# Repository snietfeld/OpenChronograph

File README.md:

# What's this?
OpenChronograph is an a Arduino-compatible hybrid smartwatch platform built around Soprod micromotors. The majority of hybrid smartwatches available today (Skagen, Fossil) use these micromotors, and many are based on the same Soprod reference design. The OpenChronograph mainboards are intended to be programmable drop-in replacements for a large number of commercial hybrid smartwatches, with a suite of handy sensors. You can also create custom dials using a process described [here](https://github.com/snietfeld/OpenChronograph/tree/master/Dials).

Platform Features:
 - Arduino-compatible Atmega328p microcontroller
 - Ultra-low-power RV-1805-C3 real-time clock
 - Precision MPU-9250 6DOF IMU + 3-axis magnetometer
 - High-precision MPL3115A2 pressure/altitude/temperature sensor
 - Support for both dual- and single-rotor micromoters (for a total of three hands)
 - Forward and retrograde hand motion
 - Custom reduced-footprint pogo-pin programmer
 
Confirmed Drop-in Compatible Watches:
 - Skagen Connected
 - Skagen Hagen
 - Fossil Q Activist
 - Fossil Q Men's Machine

# Yes, but why?
Hybrid smartwatches are neat, and they can offer fantastic battery life compared to modern smartwatches. Unfortunately, experimenting with them is difficult due to the closed nature of available designs. This project is intended to open up hybrid smartwatch design to the maker community.

# Getting started.
## What you’ll need
 - A Torx T2 driver
 - A small flathead driver
 - Watch hand pullers
 - Tweezers 
 
## Watch disassembly and board swap

## Arduino IDE Set Up
Download the Arduino IDE (tested with 1.8.9)

Clone or download this repository.

### Add the board profile
From the downloaded repository, copy the \OpenChronograph\MainBoards\oc_1\hw\Arduino_OpenChronograph_OC1 folder to your Arduino hardware folder, e.g., "C:\Program Files (x86)\Arduino\hardware\"

You should now see "OpenChronograph OC-1 (8MHz internal clock)" available in your Tools-->Board list in the Arduino IDE.

WARNING: If you skip this step, you can brick your microcontroller.

## Programming
Open the \OpenChronograph\MainBoards\oc_1\fw\oc_1_default\oc-1-default.ino project file

Select Tools --> Board --> OpenChronograph OC-1 (8MHz internal clock)

Select Tools --> Programmer --> USBtinyISP

Compile & upload using the MicroPogo programmer

 ## MicroPogo Programmer
 The MicroPogo programmer is a small-footprint Arduino serial programmer. The footprint is derived from the Protofusion [ProtoProg Programmer](http://protofusion.org/wordpress/2013/05/open-hardware-pogo-pin-programmer/), and the board is derived from TinyCircuit's [TinyLilly Mini USB Adadpter](https://tinycircuits.com/products/tinylily-mini-usb-adapter).

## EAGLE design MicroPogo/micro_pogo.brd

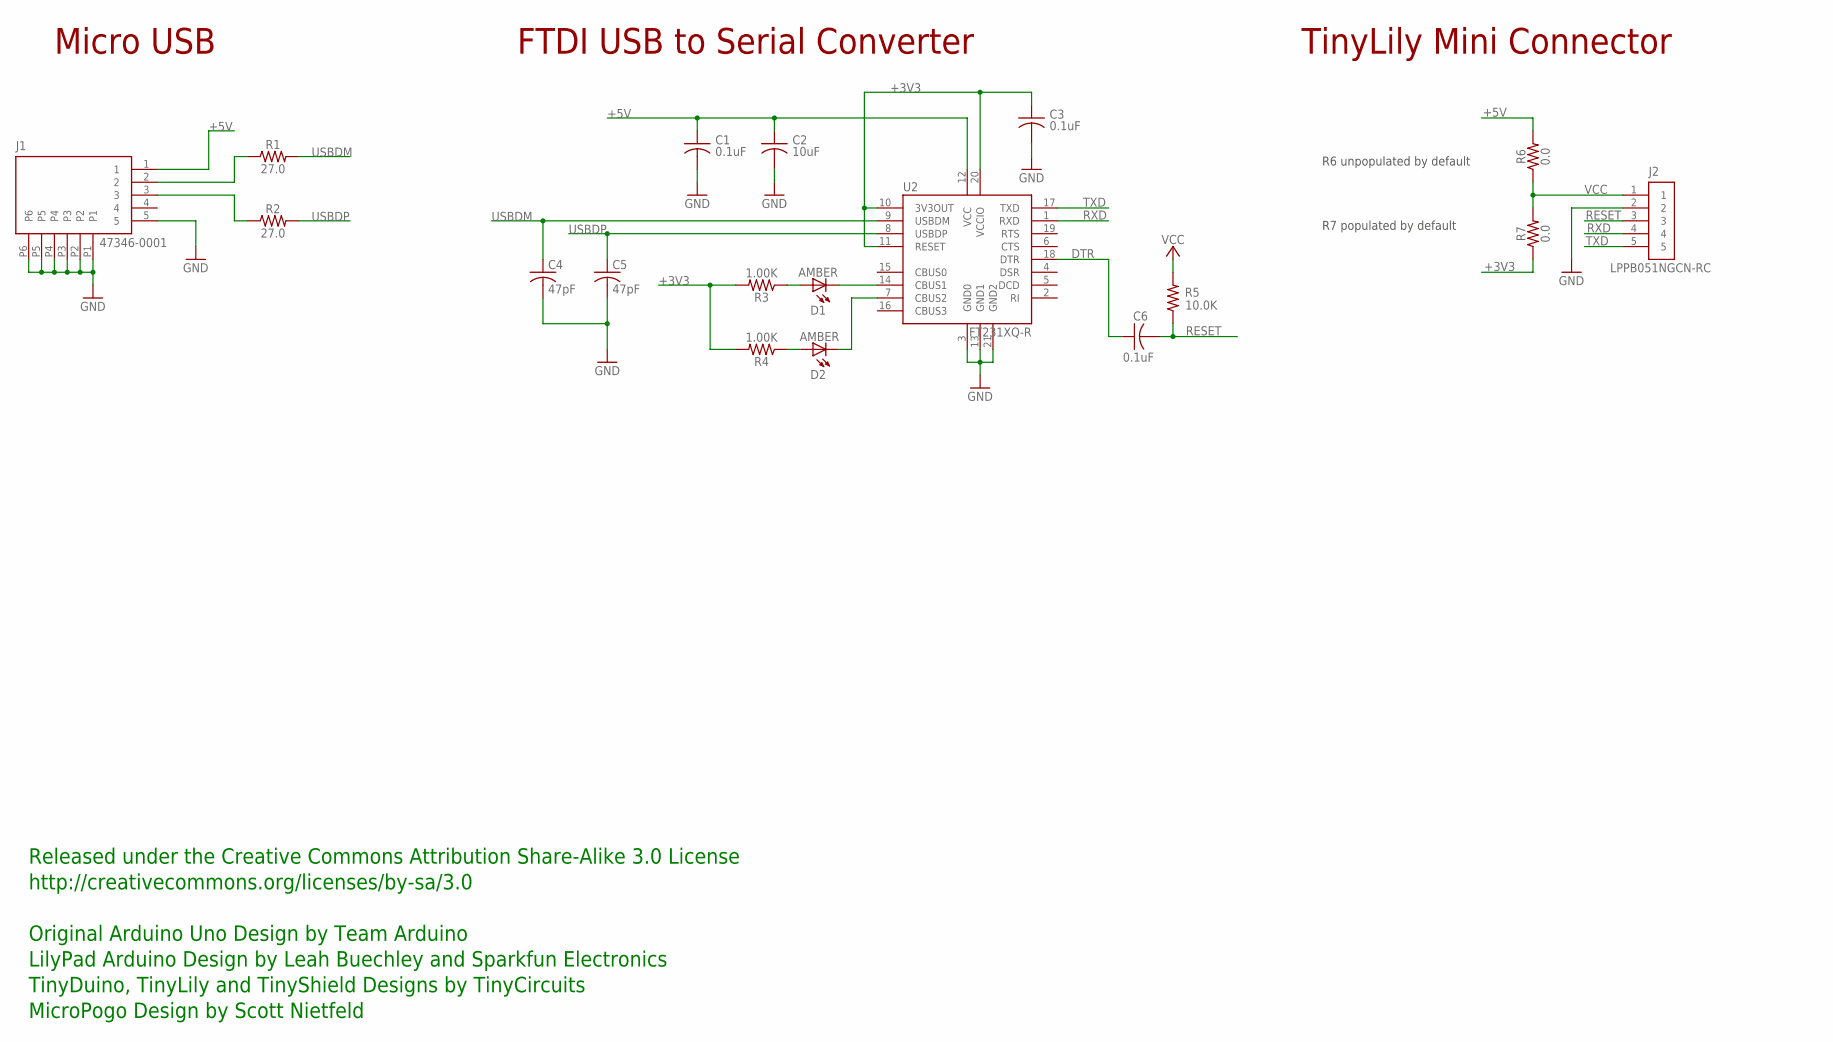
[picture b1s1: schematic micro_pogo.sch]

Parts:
C1: 0.1uF; C0402
C2: 10uF; C0603
C3, C6: 0.1uF; C0402; PARTNO AS-ITM-00008
C4, C5: 47pF; 0402; PARTNO AS-ITM-00241
D1, D2: AMBER; LNJ_LED
J1: 47346-0001; MICRO_USB; PARTNO AS-ITM-00021
J2: LPPB051NGCN-RC; 1X5_.05_RA_TH_RECPT
R1, R2: 27.0; 0402
R3, R4: 1.00K; 0402
R5: 10.0K; 0402
R6, R7: 0.0; 0402
U2: FT231XQ-R; QFN20

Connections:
+3V3: C3.1, R3.2, R4.2, R7.1, U2.10 (3V3OUT), U2.11 (RESET), U2.20 (VCCIO)
+5V: C1.1, C2.1, J1.1, R6.2, U2.12 (VCC)
DTR: C6.1, U2.18 (DTR)
GND: C1.2, C2.2, C3.2, C4.2, C5.2, J1.5, J1.P1, J1.P2, J1.P3, J1.P4, J1.P5, J1.P6, J2.2, U2.3 (GND0), U2.13 (GND1), U2.21 (GND2)
unnamed: D2.C, U2.7 (CBUS2)
unnamed: D1.A, R3.1
unnamed: D2.A, R4.1
unnamed: J1.2, R1.1
unnamed: J1.3, R2.1
unnamed: D1.C, U2.14 (CBUS1)
RESET: C6.2, J2.3, R5.1
RXD: J2.4, U2.1 (RXD)
TXD: J2.5, U2.17 (TXD)
USBDM: C4.1, R1.2, U2.9 (USBDM)
USBDP: C5.1, R2.2, U2.8 (USBDP)
VCC: J2.1, R5.2, R6.1, R7.2

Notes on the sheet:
R7 populated by default
Micro USB
FTDI USB to Serial Converter
TinyLily Mini Connector
Released under the Creative Commons Attribution Share-Alike 3.0 License
http://creativecommons.org/licenses/by-sa/3.0
Original Arduino Uno Design by Team Arduino
TinyDuino, TinyLily and TinyShield Designs by TinyCircuits
LilyPad Arduino Design by Leah Buechley and Sparkfun Electronics
R6 unpopulated by default
MicroPogo Design by Scott Nietfeld

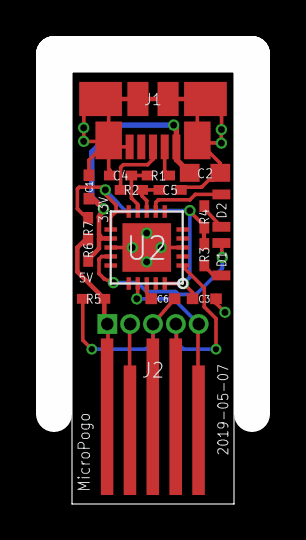
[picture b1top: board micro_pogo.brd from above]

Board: 2 copper layers, 11.0 x 24.0 mm, 18 parts (0 on the bottom side), 16 nets.

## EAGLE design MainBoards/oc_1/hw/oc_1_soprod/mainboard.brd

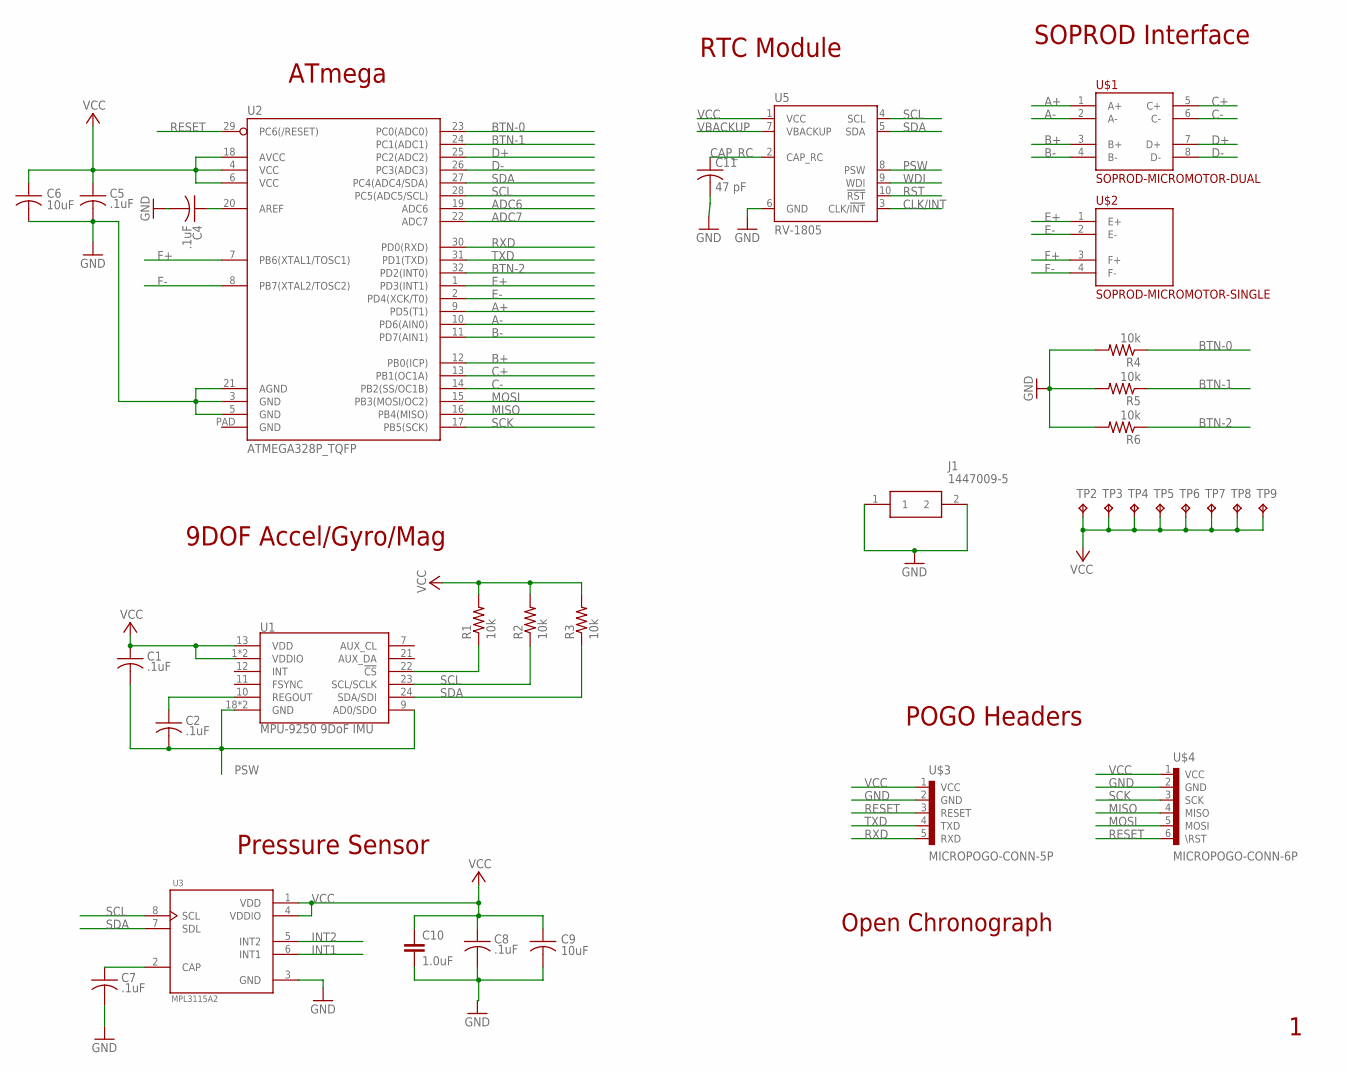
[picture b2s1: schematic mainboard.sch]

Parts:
C1, C2, C4, C5, C7, C8: .1uF; C0402
C6, C9: 10uF; C0603
C10: 1.0uF; 0402
C11: 47 pF; C0402
J1: 1447009-5; 14470095
R1, R2, R3, R4, R5, R6: 10k; R0402
TP2, TP3, TP4, TP5, TP6, TP7, TP8, TP9: TPTP15SQ; TP15SQ
U1: MPU-9250 9DoF IMU; QFN24-3X3
U2: ATMEGA328P_TQFP; MLF32-PAD
U3: MPL3115A2; PSON125P300X500X120-8N
U5: RV-1805
U$1: SOPROD-MICROMOTOR-DUAL; SOPROD-DUAL
U$2: SOPROD-MICROMOTOR-SINGLE; SOPROD-SINGLE
U$3: MICROPOGO-CONN-5P; MICROPOGO-CONN-5P-ASYM
U$4: MICROPOGO-CONN-6P; MICROPOGO-CONN-6P-ASYM

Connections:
A+: U2.9 (PD5(T1)), U$1.1 (A+)
A-: U2.10 (PD6(AIN0)), U$1.2 (A-)
ADC6: U2.19 (ADC6)
ADC7: U2.22 (ADC7)
AREF: C4.1, U2.20 (AREF)
B+: U2.12 (PB0(ICP)), U$1.3 (B+)
B-: U2.11 (PD7(AIN1)), U$1.4 (B-)
BTN-0: R4.1, U2.23 (PC0(ADC0))
BTN-1: R5.1, U2.24 (PC1(ADC1))
BTN-2: R6.1, U2.32 (PD2(INT0))
C+: U2.13 (PB1(OC1A)), U$1.5 (C+)
C-: U2.14 (PB2(SS/OC1B)), U$1.6 (C-)
CAP: C7.1, U3.2 (CAP)
CAP_RC: C11.1, U5.2 (CAP_RC)
CLK/INT: U5.3 (CLK/!INT)
D+: U2.25 (PC2(ADC2)), U$1.7 (D+)
D-: U2.26 (PC3(ADC3)), U$1.8 (D-)
E+: U2.1 (PD3(INT1)), U$2.1 (E+)
E-: U2.2 (PD4(XCK/T0)), U$2.2 (E-)
F+: U2.7 (PB6(XTAL1/TOSC1)), U$2.3 (F+)
F-: U2.8 (PB7(XTAL2/TOSC2)), U$2.4 (F-)
GND: C4.2, C5.2, C6.2, C7.2, C8.2, C9.2, C10.2, C11.2, J1.1, J1.2, R4.2, R5.2, R6.2, U2.3 (GND), U2.5 (GND), U2.21 (AGND), U3.3 (GND), U5.6 (GND), U$3.2 (GND), U$4.2 (GND)
INT1: U3.6 (INT1)
INT2: U3.5 (INT2)
MISO: U2.16 (PB4(MISO)), U$4.4 (MISO)
MOSI: U2.15 (PB3(MOSI/OC2)), U$4.5 (MOSI)
unnamed: C2.1, U1.10 (REGOUT)
unnamed: R1.1, U1.22 (!CS)
PSW: C1.2, C2.2, U1.9 (AD0/SDO), U1.18 (GND), U1.20 (GND), U5.8 (PSW)
RESET: U2.29 (PC6(/RESET)), U$3.3 (RESET), U$4.6 (\RST)
RST: U5.10 (!RST)
RXD: U2.30 (PD0(RXD)), U$3.5 (RXD)
SCK: U2.17 (PB5(SCK)), U$4.3 (SCK)
SCL: R2.1, U1.23 (SCL/SCLK), U2.28 (PC5(ADC5/SCL)), U3.8 (SCL), U5.4 (SCL)
SDA: R3.1, U1.24 (SDA/SDI), U2.27 (PC4(ADC4/SDA)), U3.7 (SDL), U5.5 (SDA)
TXD: U2.31 (PD1(TXD)), U$3.4 (TXD)
VBACKUP: U5.7 (VBACKUP)
VCC: C1.1, C5.1, C6.1, C8.1, C9.1, C10.1, R1.2, R2.2, R3.2, TP2.TP, TP3.TP, TP4.TP, TP5.TP, TP6.TP, TP7.TP, TP8.TP, TP9.TP, U1.1 (VDDIO), U1.8 (VDDIO), U1.13 (VDD), U2.4 (VCC), U2.6 (VCC), U2.18 (AVCC), U3.1 (VDD), U3.4 (VDDIO), U5.1 (VCC), U$3.1 (VCC), U$4.1 (VCC)
WDI: U5.9 (WDI)

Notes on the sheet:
ATmega
Open Chronograph
SOPROD Interface
9DOF Accel/Gyro/Mag
Pressure Sensor
RTC Module
POGO Headers

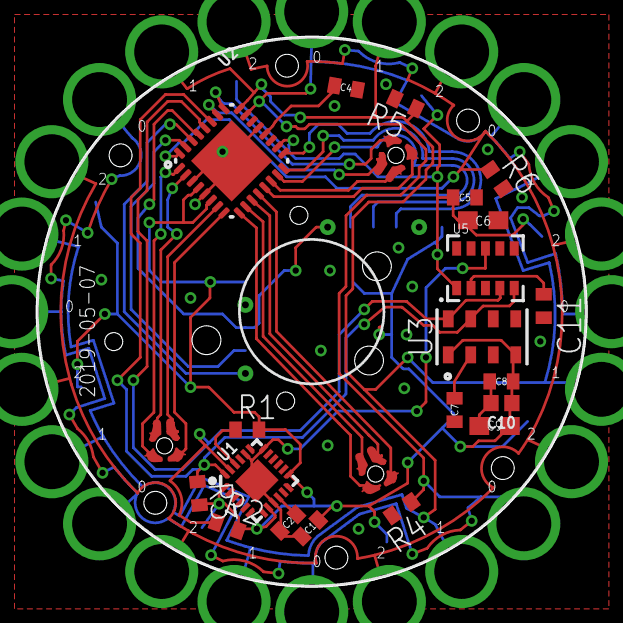
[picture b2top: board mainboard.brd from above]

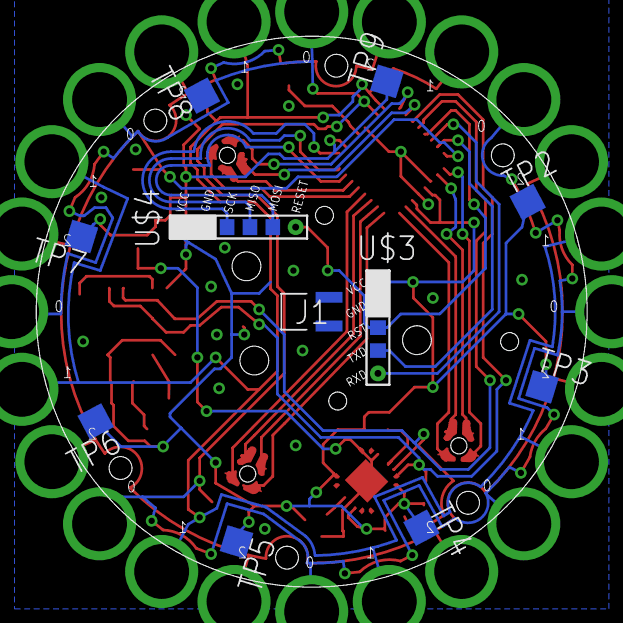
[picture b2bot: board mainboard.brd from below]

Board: 2 copper layers, 30.6 x 30.6 mm, 33 parts (11 on the bottom side), 31 nets.

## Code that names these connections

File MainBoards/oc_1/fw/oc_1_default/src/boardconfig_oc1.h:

#ifndef __BOARDCONFIG_MARK_II_H__
#define __BOARDCONFIG_MARK_II_H__

#ifdef __cplusplus
extern "C" {
#endif

#include <pins_arduino.h>
#include "boardconfig.h"

// Pin Mapping Table
//--------------------------------------------------------------------------------
//Phys Pin    ID    Arduino Pin
// 1          PC6     RESET
// 2          PD0       0     (RX)
// 3          PD1       1     (TX)
// 4          PD2       2
// 5          PD3       3
// 6          PD4       4
// 7          VCC
// 8          GND
// 9          PB6       xtal1
// 10         PB7       xtal2
// 11         PD5       5
// 12         PD6       6
// 13         PD7       7
// 14         PB0       8
// 15         PB1       9
// 16         PB2       10
// 17         PB3       11
// 18         PB4       12
// 19         PB5       13
// 20         AVCC
// 21         AREF
// 22         GND
// 23         PC0       14    (A0)
// 24         PC1       15    (A1)
// 25         PC2       16    (A2)
// 26         PC3       17    (A3)
// 27         PC4       18    (A4)
// 28         PC5       19    (A5)

// ATMEL ATMEGA8 & 168 / ARDUINO
//
//                  +-\/-+
//            PC6  1|    |28  PC5 (AI 5)
//      (D 0) PD0  2|    |27  PC4 (AI 4)
//      (D 1) PD1  3|    |26  PC3 (AI 3)
//      (D 2) PD2  4|    |25  PC2 (AI 2)
// PWM+ (D 3) PD3  5|    |24  PC1 (AI 1)
//      (D 4) PD4  6|    |23  PC0 (AI 0)
//            VCC  7|    |22  GND
//            GND  8|    |21  AREF
//            PB6  9|    |20  AVCC
//            PB7 10|    |19  PB5 (D 13)
// PWM+ (D 5) PD5 11|    |18  PB4 (D 12)
// PWM+ (D 6) PD6 12|    |17  PB3 (D 11) PWM
//      (D 7) PD7 13|    |16  PB2 (D 10) PWM
//      (D 8) PB0 14|    |15  PB1 (D 9) PWM
//                  +----+

// MR0 - Minute Hand, Reverse Drive, Contact 0
// MR1 - Minute Hand, Reverse Drive, Contact 1
// MF0 - Minute Hand, Forward Drive, Contact 0
// ...
// HF1 - Hour Hand, Forward Drive, Contact 1

#define N_DIO_PINS 15
  
const DigitalPin pin_cfg[] = {
  {&PORTC, &DDRC, PC2, DDC2, OUTPUT, MOTOR_HF0, 0},
  {&PORTC, &DDRC, PC3, DDC3, OUTPUT, MOTOR_HF1, 0},
  {&PORTB, &DDRB, PB1, DDB1, OUTPUT, MOTOR_HR0, 0},
  {&PORTB, &DDRB, PB2, DDB2, OUTPUT, MOTOR_HR1, 0},

  {&PORTB, &DDRB, PB0, DDB0, OUTPUT, MOTOR_MF0, 0},
  {&PORTD, &DDRD, PD7, DDD7, OUTPUT, MOTOR_MF1, 0},
  {&PORTD, &DDRD, PD5, DDD5, OUTPUT, MOTOR_MR0, 0},
  {&PORTD, &DDRD, PD6, DDD6, OUTPUT, MOTOR_MR1, 0},

  {&PORTB, &DDRB, PB6, DDB6, OUTPUT, MOTOR_SF0, 0},
  {&PORTB, &DDRB, PB7, DDB7, OUTPUT, MOTOR_SF1, 0},
  {&PORTD, &DDRD, PD3, DDD3, OUTPUT, MOTOR_SR0, 0},
  {&PORTD, &DDRD, PD4, DDD4, OUTPUT, MOTOR_SR1, 0},

  {&PORTC, &DDRC, A0,  DDC0, INPUT, BUTTON_DECR, 0},
  {&PORTC, &DDRC, A1,  DDC1, INPUT, BUTTON_MODE, 0},
  {&PORTD, &DDRD, PD2, DDD2, INPUT, BUTTON_INCR, 0},
};


  

#ifdef __cplusplus
} // extern "C"
#endif

#endif // __BOARDCONFIG_MARK_II_H__

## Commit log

2020-01-08 Initial commit of oc-1 files.
2020-01-12 Added svgviewer and aero dial example.
2020-01-13 Added pictures of bare dial pcbs and paint.
2020-01-13 Fix typo
2020-01-13 Added spacer ring and caliper photos
2020-01-13 Added a couple more dial examples.
2020-01-13 Quick fix for aero dial.
2020-01-13 Update dial howto

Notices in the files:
parts and their libraries:
SparkFun-IC-Microcontroller: Licensing: Creative Commons ShareAlike 4.0 International - https://creativecommons.org/licenses/by-sa/4.0
